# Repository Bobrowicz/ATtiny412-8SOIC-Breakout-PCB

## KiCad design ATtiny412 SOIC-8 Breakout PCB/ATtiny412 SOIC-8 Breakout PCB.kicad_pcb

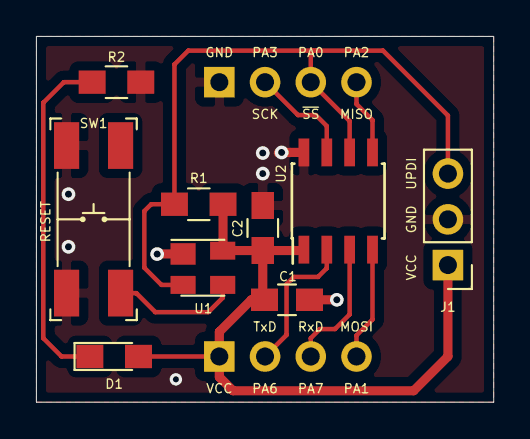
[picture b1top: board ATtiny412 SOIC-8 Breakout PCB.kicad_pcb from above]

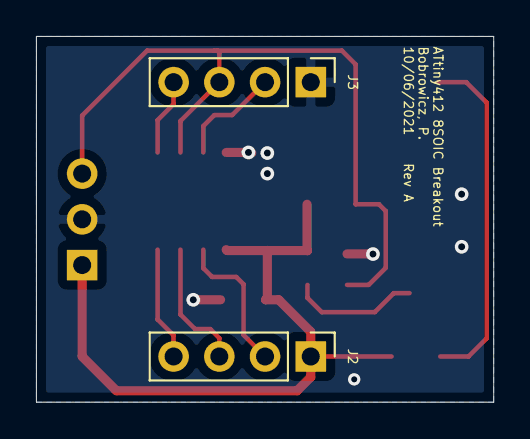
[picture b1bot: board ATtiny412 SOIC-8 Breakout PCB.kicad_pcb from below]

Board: 2 copper layers, 25.4 x 20.3 mm, 11 parts (2 on the bottom side), 10 nets.

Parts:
C1: 1u; C_0805_HandSoldering
C2: 100n; C_0805_HandSoldering
D1: LED; LED_0805_HandSoldering
J1: Conn_01x03_Male; Pin_Header_Straight_1x03_Pitch2.54mm
J2, J3: Conn_01x04_Male; Pin_Header_Straight_1x04_Pitch2.54mm
R1: 10k; R_0805_HandSoldering
R2: 470R; R_0805_HandSoldering
SW1: SW_MEC_5E; TL3305AF160QG
U1: MIC6315; SOT-143
U2: ATtiny412-SS; SOIC-8_3.9x4.9mm_Pitch1.27mm

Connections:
/AIN0: J1.3, J3.3, R1.2, U1.2, U2.6
/AIN1: J2.4, U2.4
/AIN2: J3.4, U2.5
/AIN3: J3.2, U2.7
/AIN6: J2.2, U2.2
/AIN7: J2.3, U2.3
/~MR: SW1.1, U1.3
GND: C1.2, C2.2, J1.2, J3.1, R2.2, SW1.3, SW1.4, U1.1, U2.8
unnamed: D1.1, R2.1
VCC: C1.1, C2.1, D1.2, J1.1, J2.1, R1.1, U1.4, U2.1

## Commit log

2021-08-21 Renamed files, minor fixes.
    Corrected silk screen, and net names.
